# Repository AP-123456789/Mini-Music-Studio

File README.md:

# Mini Music Studio MIDI Controller

A compact, custom-designed USB MIDI controller built completely from scratch around the Waveshare ESP32-S3-Zero microcontroller. Designed as an intensive beginner learning project in KiCad 10.0 and PlatformIO, this project documents a 35-hour journey of trial, error, troubleshooting, and iteration in custom PCB design, schematic capture, dual-layer trace routing, and embedded C++ firmware development.

---

## What the Product Does
The **Mini Music Studio** is an interactive hardware input device that connects directly to a computer via USB to interface with Digital Audio Workstations (DAWs) and music production software. It serves several core functions:
* **Tactile Note Triggering:** Features 12 Kailh Choc low-profile mechanical key switches arranged in a 3x4 multiplexed anti-ghosting diode matrix to play musical notes, trigger drum samples, or launch audio clips.
* **Continuous Parameter Control:** Integrates two slide potentiometers to allow live, continuous adjustment of audio parameters such as track volume, filter cutoff, modulation, or expression.
* **Navigation & Effect Adjustment:** Incorporates two EC11 rotary encoders with push switches to scroll through menus, select instrument patches, or fine-tune effect intensities.
* **Dynamic Per-Key Backlighting:** Utilizes 12 addressable SK6812 MINI-E RGB NeoPixels mounted in a serial daisy-chain to provide real-time visual feedback, key identification, and custom lighting animations.
* **Auxiliary Touch Controls:** Employs four capacitive-touch pad headers to execute quick macro commands, switch control banks, or toggle lighting modes.
* **Native USB Processing:** Powered by an onboard Waveshare ESP32-S3-Zero running custom C++ firmware that processes all hardware inputs and transmits standard USB MIDI messages over USB.

---

## Development Journey & Process (35-Hour Breakdown)
Building this project as a beginner required immense patience, troubleshooting, and continuous reference to official documentation and developer communities:
1. **Project Initialization & Library Setup (Hours 0–1):** Opened KiCad 10.0 for the first time, established the project draft, and struggled through path substitutions to register external custom symbol and footprint libraries from the [Hackclub KiCad Libraries Repository](https://github.com/hackclub/Hackclub-KiCad-Libraries).

2. **Schematic Capture & Component Placement (Hours 1–5):** Placed 12 push-button switch symbols, the ESP32-S3-Zero microcontroller (`U1`), slide potentiometers (`RV1`, `RV2`), rotary encoders (`SW13`, `SW14`), 12 SK6812 MINI-E LEDs (`D1`–`D12`), and touch headers (`J1`–`J4`). Cross-checked pin mappings against the [Waveshare ESP32-S3-Zero Wiki & Pinout Guide](https://www.waveshare.com/wiki/ESP32-S3-Zero).

3. **Switch Matrix & Diode Wiring (Hours 5–13):** Paired 12 `D_Small` anti-ghosting diodes (`D13`–`D24`) with the switches and organized complex routing using clean `ROW1`–`ROW3` and `COL1`–`COL4` net labels. Wired encoder quadrature signals (`ENC1_A`, `ENC1_B`, `ENC2_A`, `ENC2_B`) and analog wiper outputs (`POT1_OUT`, `POT2_OUT`).

4. **LED Daisy-Chaining & ERC Cleanup (Hours 13–20):** Serialized the SK6812 MINI-E LEDs from `DOUT` to `DIN`, handled pin conflicts by re-assigning GPIOs, and resolved electrical rules check (ERC) warnings by adding `PWR_FLAG` symbols and No Connect markers.

5. **Footprint Assignment & PCB Layout (Hours 20–30):** Matched abstract schematic symbols to exact physical footprints, arranged components on the canvas within an `Edge.Cuts` board boundary, and routed dual-layer copper traces (`F.Cu` and `B.Cu`). Resolved track width violations and closed-loop outline errors to achieve a zero-error Design Rules Check (DRC).

6. **Manufacturing Files & 3D Render (Hours 30–32):** Inspected the board in KiCad's 3D Viewer, plotted production Gerbers and drill files, and generated BOM/CPL packages using the [JLCPCB Fabrication Toolkit](https://jlcpcb.com/).

7. **Firmware Development & USB MIDI (Hours 32–35):** Configured PlatformIO in VS Code using the [PlatformIO ESP32 Build System Guide](https://docs.platformio.org/). Wrote modular C++ drivers for matrix polling, FastLED animations (referencing the [FastLED Animation Library Documentation](https://fastled.io/docs/)), and integrated USB MIDI message transmission following the [MIDI Association USB MIDI Specification](https://www.midi.org/specifications).

---

## Bill of Materials (BOM) & Estimated Costs

| Item No. | Item | Designator | Quantity | Purpose | Unit Price ($) | Total Price ($) | Vendor | Vendor Link |
| :---: | :--- | :---: | :---: | :--- | :---: | :---: | :---: | :--- |
| **1** | ESP32-S3 Microcontroller Module | U1 | 1 | Main MCU controller & USB MIDI interface | $4.50 | $4.50 | JLCPCB / LCSC | [JLCPCB Sourcing](https://jlcpcb.com/) |
| **2** | Kailh Choc Low-Profile Switches | SW1–SW12 | 12 | Primary musical key switches | $0.75 | $9.00 | JLCPCB / LCSC | [JLCPCB Sourcing](https://jlcpcb.com/) |
| **3** | SK6812 MINI-E RGB LEDs | D1–D12 | 12 | Per-key RGB backlight illumination | $0.20 | $2.40 | JLCPCB / LCSC | [JLCPCB Sourcing](https://jlcpcb.com/) |
| **4** | 10k Slide Potentiometers | RV1, RV2 | 2 | Continuous analog parameter controls | $1.10 | $2.20 | JLCPCB / LCSC | [JLCPCB Sourcing](https://jlcpcb.com/) |
| **5** | EC11 Rotary Encoders w/ Switch | SW13, SW14 | 2 | Parameter adjustment & navigation | $1.00 | $2.00 | JLCPCB / LCSC | [JLCPCB Sourcing](https://jlcpcb.com/) |
| **6** | 1N4148 SOD-123 Diodes | D13–D24 | 12 | Matrix anti-ghosting switching diodes | $0.03 | $0.36 | JLCPCB / LCSC | [JLCPCB Sourcing](https://jlcpcb.com/) |
| **7** | 1x01 Pin Headers (Touch Pads) | J1–J4 | 4 | Placeholders for capacitive touch areas | $0.15 | $0.60 | JLCPCB / LCSC | [JLCPCB Sourcing](https://jlcpcb.com/) |
| **8** | Custom Printed PCB (Dual-Layer) | PCB | 1 | Circuit board fabrication (5-pack share) | $2.54 | $2.54 | JLCPCB | [JLCPCB Fabrication](https://jlcpcb.com/) |

---

## Firmware Setup & Usage
The firmware is written in C++ using PlatformIO on the Arduino framework.

1. Open the project folder in Visual Studio Code with the PlatformIO extension installed.
2. Connect the Waveshare ESP32-S3-Zero to your computer via USB.
3. Build and upload the firmware binary:
   ```bash
   pio run --target upload

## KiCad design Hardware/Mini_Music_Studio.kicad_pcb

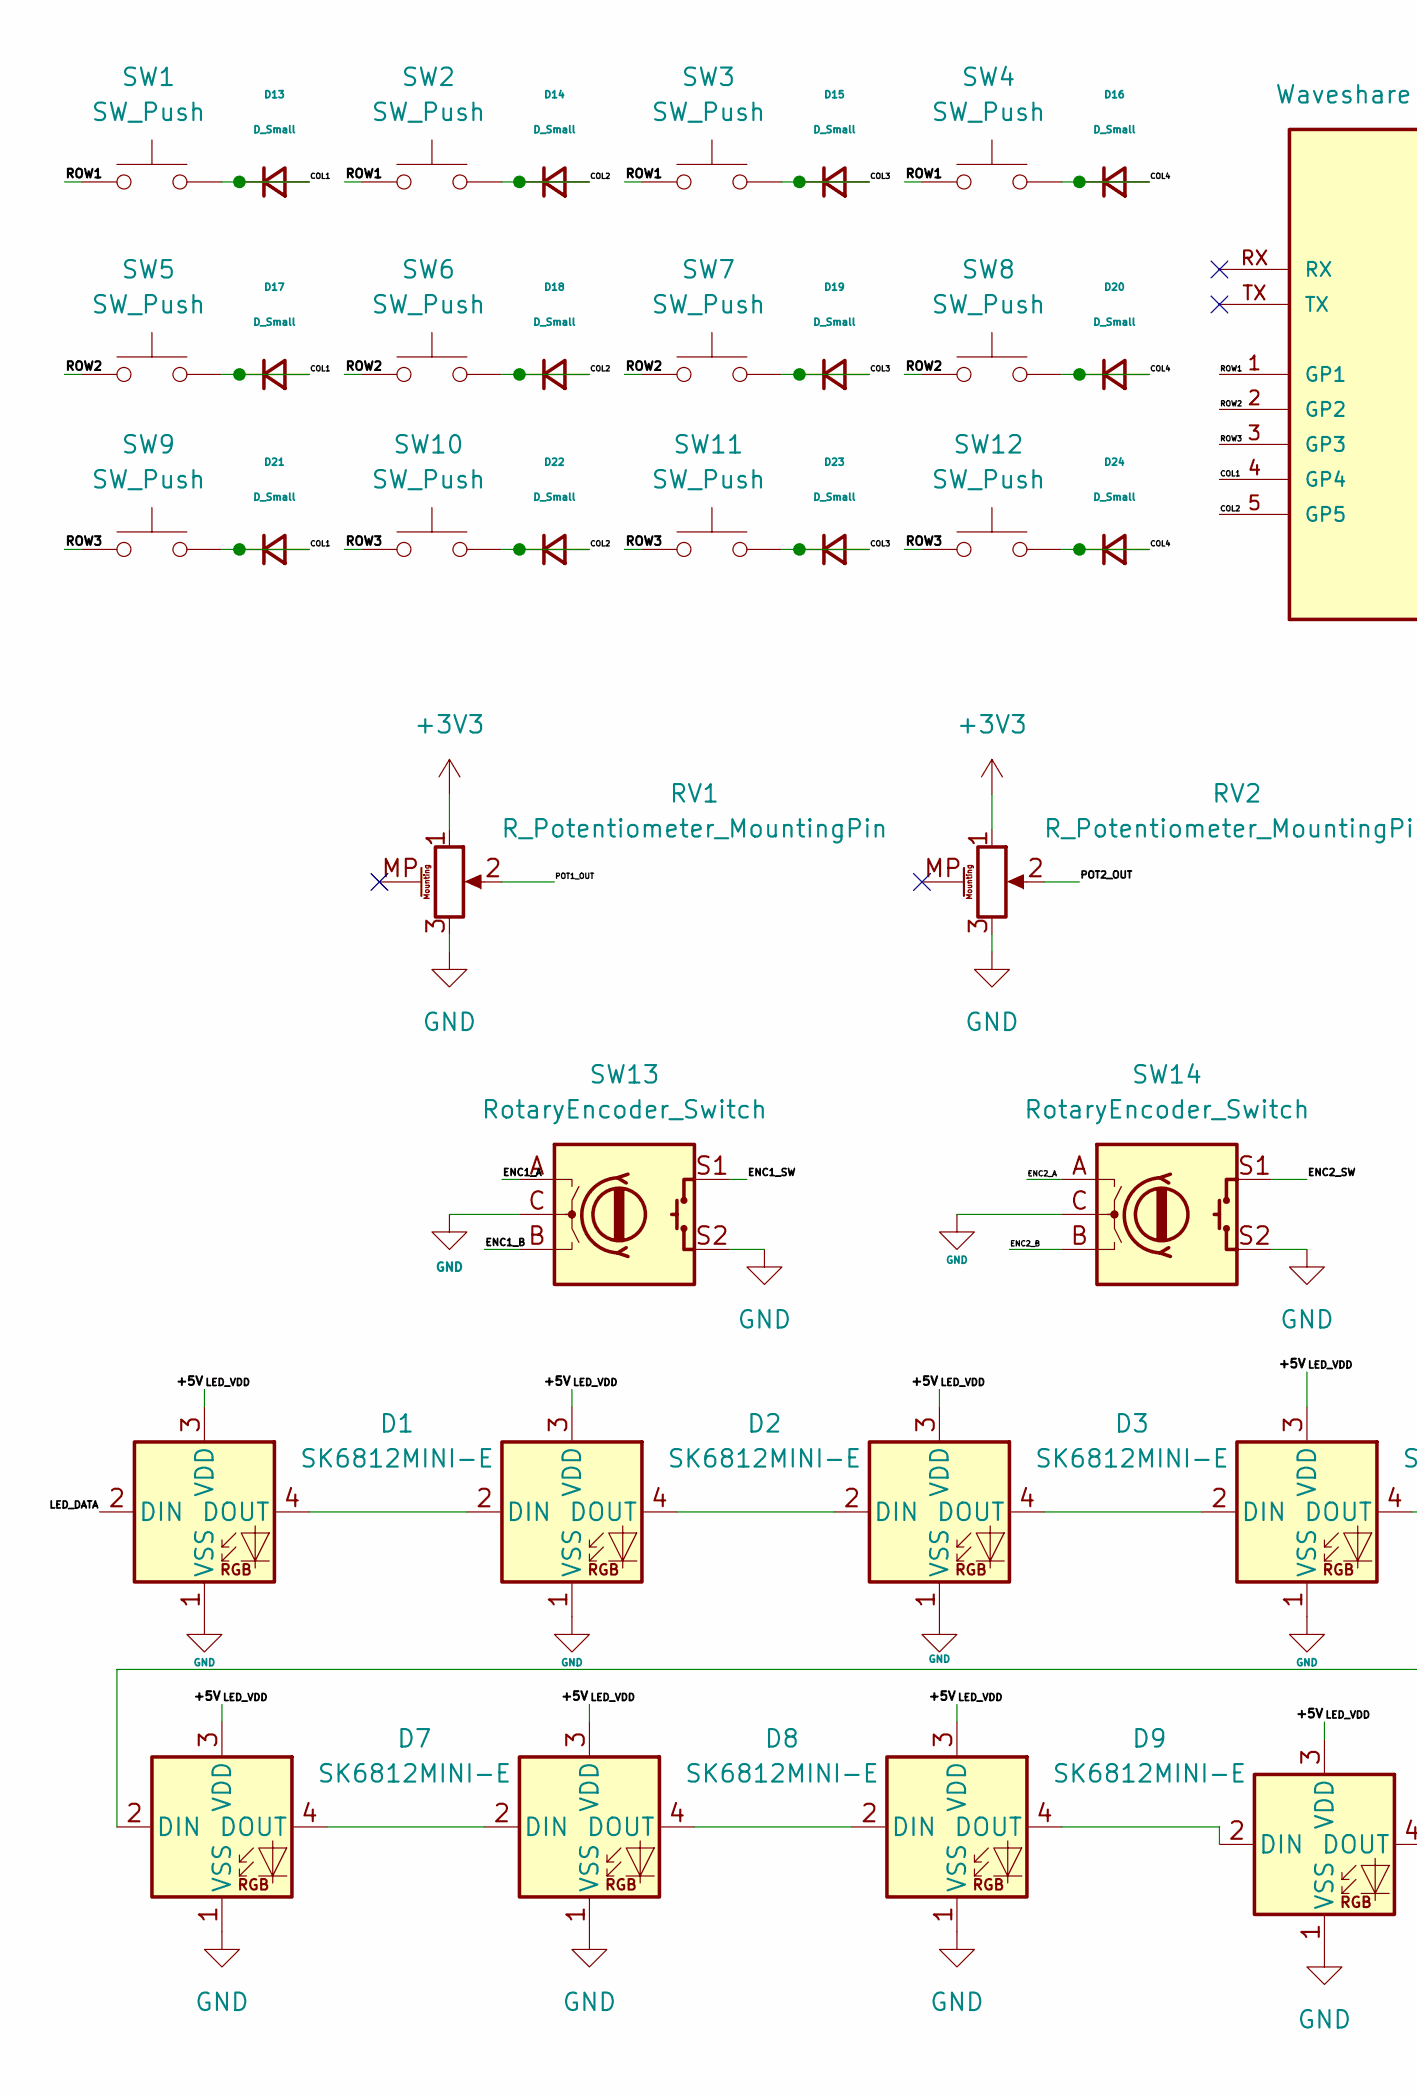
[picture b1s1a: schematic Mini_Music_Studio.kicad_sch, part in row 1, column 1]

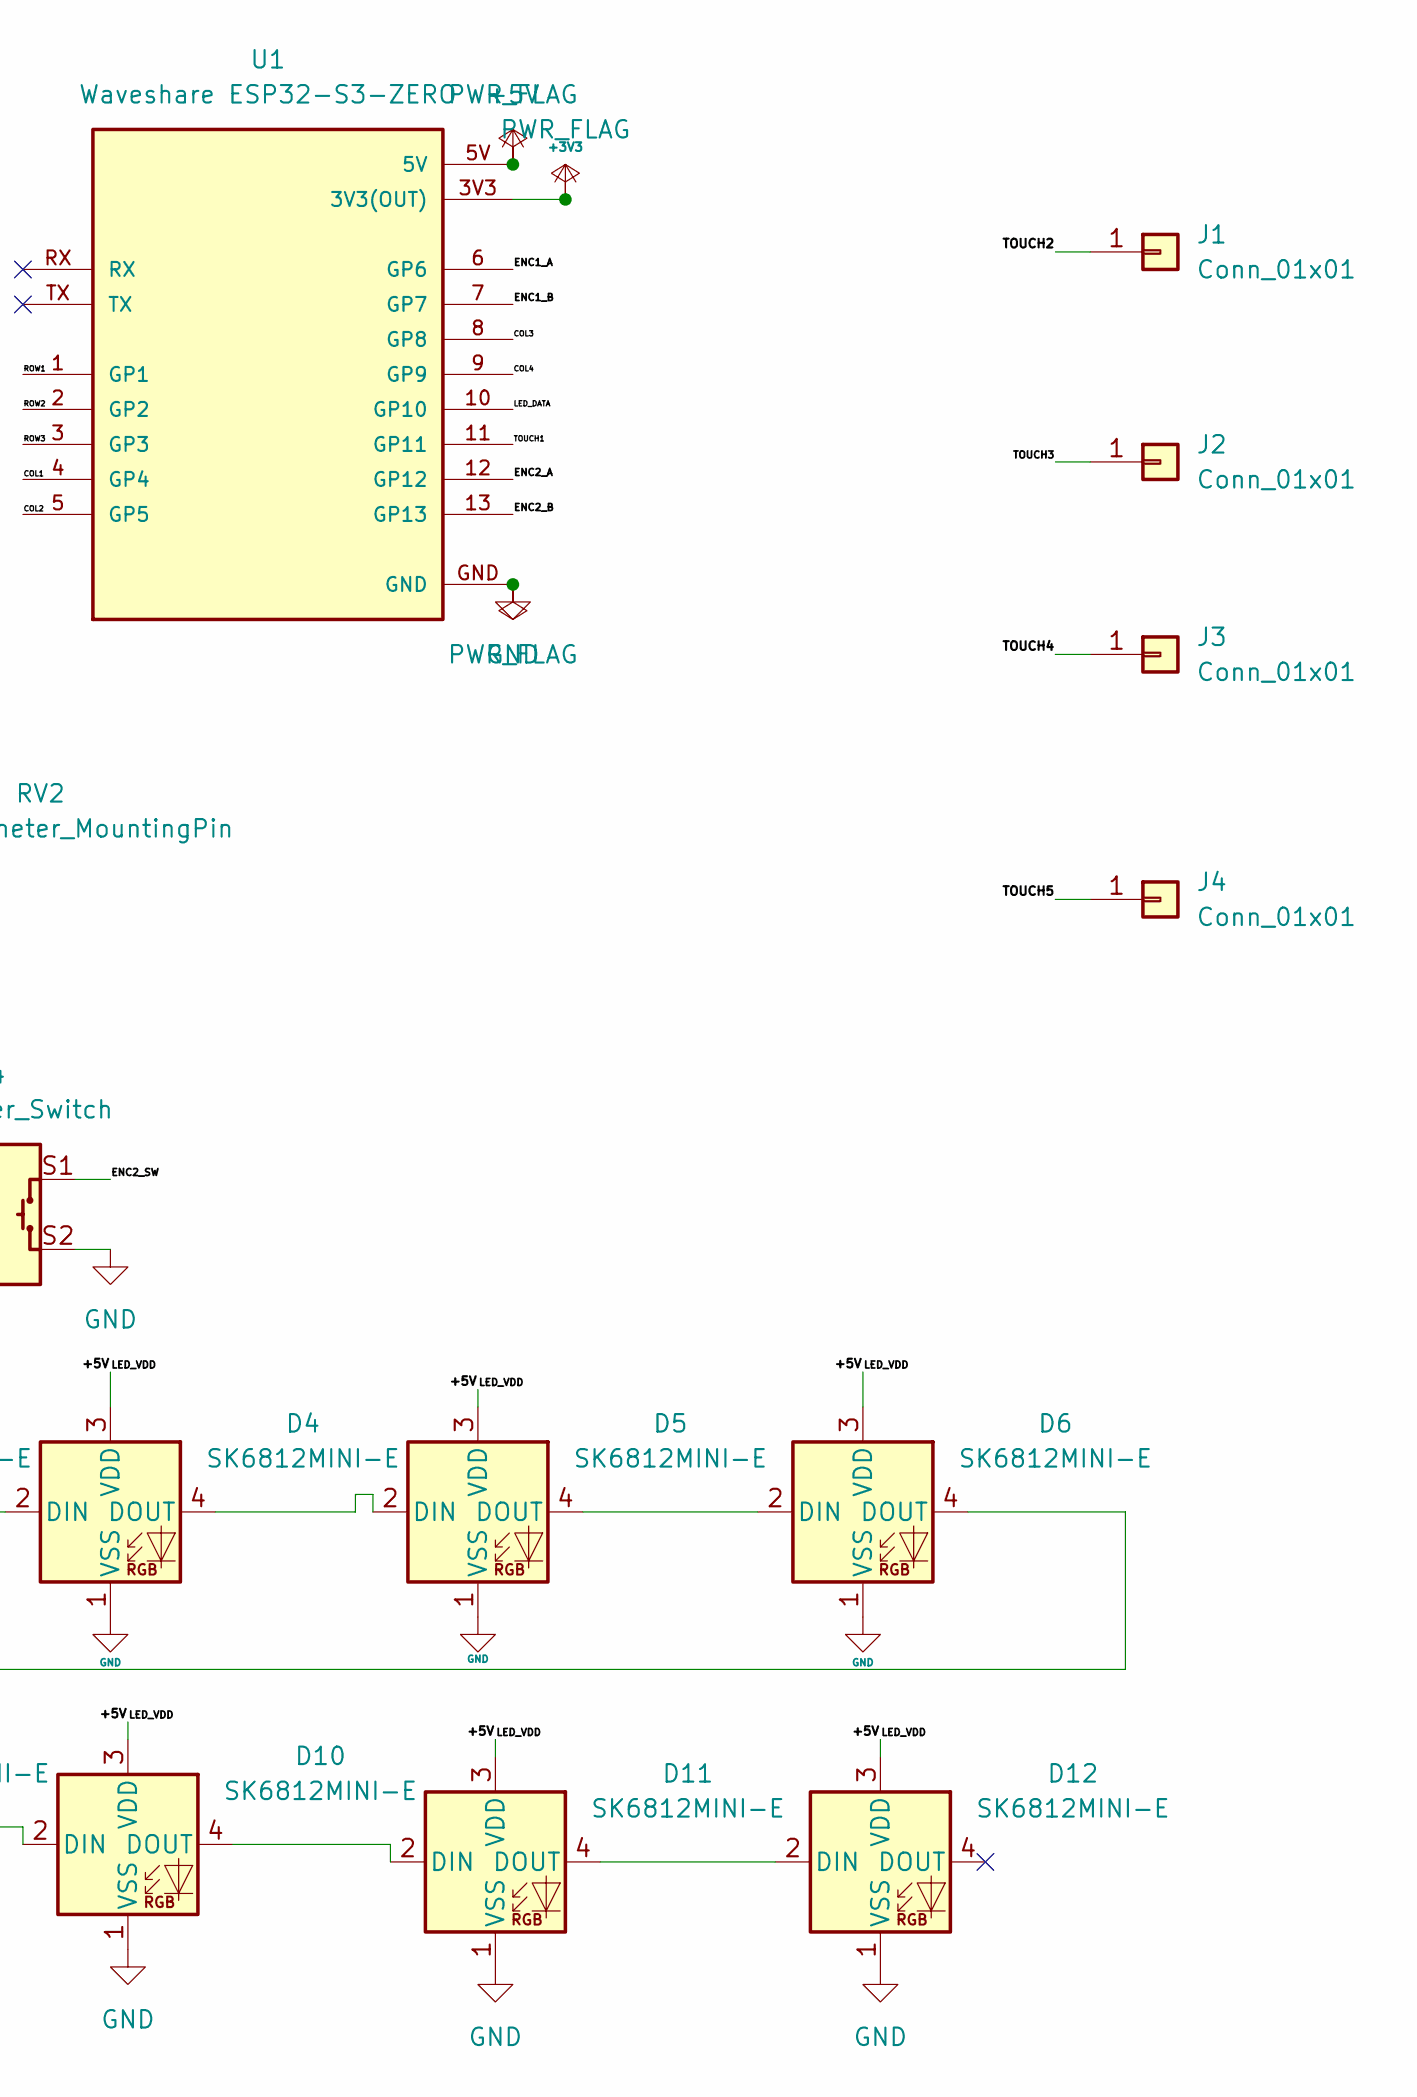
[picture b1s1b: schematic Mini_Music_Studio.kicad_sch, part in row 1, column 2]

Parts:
D1, D2, D3, D4, D5, D6, D7, D8, D9, D10, D11, D12: SK6812MINI-E; LED_SK6812MINI-E_3.2x2.8mm_P1.5mm_ReverseMount
D13, D14, D15, D16, D17, D18, D19, D20, D21, D22, D23, D24: D_Small; D_DO-35_SOD27_P7.62mm_Horizontal
J1, J2, J3, J4: Conn_01x01; PinHeader_1x01_P2.54mm_Vertical
RV1, RV2: R_Potentiometer_MountingPin; Potentiometer_Bourns_PTA1543_Single_Slide
SW1, SW2, SW3, SW4, SW5, SW6, SW7, SW8, SW9, SW10, SW11, SW12: SW_Push; Kailh Choc Low-Profile Switches
SW13, SW14: RotaryEncoder_Switch; RotaryEncoder_Alps_EC11E-Switch_Vertical_H20mm
U1: Waveshare ESP32-S3-ZERO; Waveshare ESP32-S3-Zero; PARTREV NA

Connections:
+3V3: RV1.1, RV2.1, U1.3V3 (3V3(OUT))
+5V: D1.3 (VDD), D2.3 (VDD), D3.3 (VDD), D4.3 (VDD), D5.3 (VDD), D6.3 (VDD), D7.3 (VDD), D8.3 (VDD), D9.3 (VDD), D10.3 (VDD), D11.3 (VDD), D12.3 (VDD), U1.5V
/COL1: D13.1 (K), D13.2 (A), D17.1 (K), D17.2 (A), D21.1 (K), D21.2 (A), SW1.2, SW5.2, SW9.2, U1.4 (GP4)
/COL2: D14.1 (K), D14.2 (A), D18.1 (K), D18.2 (A), D22.1 (K), D22.2 (A), SW2.2, SW6.2, SW10.2, U1.5 (GP5)
/COL3: D15.1 (K), D15.2 (A), D19.1 (K), D19.2 (A), D23.1 (K), D23.2 (A), SW3.2, SW7.2, SW11.2, U1.8 (GP8)
/COL4: D16.1 (K), D16.2 (A), D20.1 (K), D20.2 (A), D24.1 (K), D24.2 (A), SW4.2, SW8.2, SW12.2, U1.9 (GP9)
/ENC1_A: SW13.A, U1.6 (GP6)
/ENC1_B: SW13.B, U1.7 (GP7)
/ENC1_SW: SW13.S1
/ENC2_A: SW14.A, U1.12 (GP12)
/ENC2_B: SW14.B, U1.13 (GP13)
/ENC2_SW: SW14.S1
/LED_DATA: D1.2 (DIN), U1.10 (GP10)
/POT1_OUT: RV1.2
/POT2_OUT: RV2.2
/ROW1: SW1.1, SW2.1, SW3.1, SW4.1, U1.1 (GP1)
/ROW2: SW5.1, SW6.1, SW7.1, SW8.1, U1.2 (GP2)
/ROW3: SW9.1, SW10.1, SW11.1, SW12.1, U1.3 (GP3)
/TOUCH1: U1.11 (GP11)
/TOUCH2: J1.1 (Pin_1_1)
/TOUCH3: J2.1 (Pin_1_1)
/TOUCH4: J3.1 (Pin_1_1)
/TOUCH5: J4.1 (Pin_1_1)
GND: D1.1 (VSS), D2.1 (VSS), D3.1 (VSS), D4.1 (VSS), D5.1 (VSS), D6.1 (VSS), D7.1 (VSS), D8.1 (VSS), D9.1 (VSS), D10.1 (VSS), D11.1 (VSS), D12.1 (VSS), RV1.3, RV2.3, SW13.C, SW13.S2, SW14.C, SW14.S2, U1.GND
unnamed: D1.4 (DOUT), D2.2 (DIN)
unnamed: D2.4 (DOUT), D3.2 (DIN)
unnamed: D3.4 (DOUT), D4.2 (DIN)
unnamed: D4.4 (DOUT), D5.2 (DIN)
unnamed: D5.4 (DOUT), D6.2 (DIN)
unnamed: D6.4 (DOUT), D7.2 (DIN)
unnamed: D7.4 (DOUT), D8.2 (DIN)
unnamed: D8.4 (DOUT), D9.2 (DIN)
unnamed: D9.4 (DOUT), D10.2 (DIN)
unnamed: D10.4 (DOUT), D11.2 (DIN)
unnamed: D11.4 (DOUT), D12.2 (DIN)

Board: 2 copper layers, 45 parts (0 on the bottom side), 26 nets, no tracks yet.

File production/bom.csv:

Designator,Footprint,Quantity,Value,LCSC Part #
"D1, D10, D11, D12, D2, D3, D4, D5, D6, D7, D8, D9",LED_SK6812MINI-E_3.2x2.8mm_P1.5mm_ReverseMount,12,SK6812MINI-E,
"D13, D14, D15, D16, D17, D18, D19, D20, D21, D22, D23, D24",D_DO-35_SOD27_P7.62mm_Horizontal,12,D_Small,
"J1, J2, J3, J4",PinHeader_1x01_P2.54mm_Vertical,4,Conn_01x01,
"RV1, RV2",Potentiometer_Bourns_PTA1543_Single_Slide,2,R_Potentiometer_MountingPin,
"SW1, SW10, SW11, SW12, SW2, SW3, SW4, SW5, SW6, SW7, SW8, SW9",Kailh Choc Low-Profile Switches,12,SW_Push,
"SW13, SW14",RotaryEncoder_Alps_EC11E-Switch_Vertical_H20mm,2,RotaryEncoder_Switch,
U1,Waveshare ESP32-S3-Zero,1,Waveshare ESP32-S3-ZERO,
